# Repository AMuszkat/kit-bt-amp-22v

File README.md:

# kit_bt_amp_22v

A reference design demonstrating the **MA12070P amplifier** for portable applications, combining a **PSoC 6 MCU** with a **CYW-series Bluetooth module**.

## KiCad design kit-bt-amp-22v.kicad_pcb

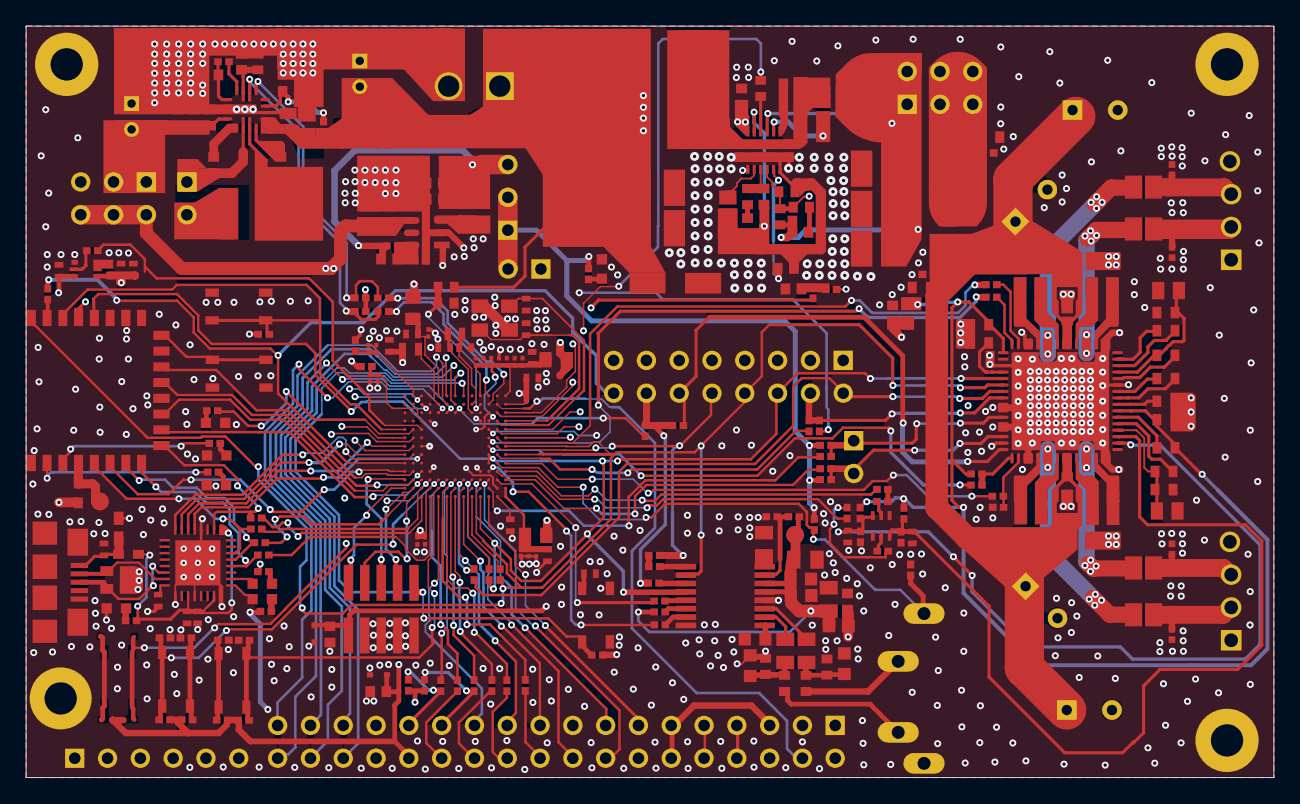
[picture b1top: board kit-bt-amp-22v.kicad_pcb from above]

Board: 4 copper layers, 96.6 x 58.2 mm, 274 parts (0 on the bottom side), 221 nets.

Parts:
C0A, C0B, C1A, C1B: C0402C471K5RAC; CAPC0402(1005)60_L
C1, C8, C19, C34, C80: CL10B104KB8NNNC; CAPC1608X90X30LL10T20
C2, C3, C4, C6, C7: GMK325BJ226MM-P; CAP1210_IPC_B
C5: EMZR350ARA470ME61G; PNSC-FT-V-53x53-2_V
C9, C11: CAPC1608X90X30LL10T20
C10: UMK212BB7225KG-T; CAPC2013X145X50LL20T25
C12: GRM1885C1H103JA01D; CAPC1608X90X30LL10T20
C13: GRM1885C1H682JA01D; CAPC1608X90X30LL10T20
C14, C16, C23, C26: CL05B104KA5NNNC; CAPC1608X90X30LL10T20
C15, C18: GRM21BR61E226ME44L; CAP0805_IPC_B
C17, C25: EST476M025AC3AA; FP-UPW1E220MDD-MFG
C20, C21, C27, C28: GRM188R61E106KA73J; CAP0603_IPC_C
C22: UMK105CG220JV-F; CAPC1608X90X30LL10T20
C24, C30: CL05B223KA5NNNC; CAPC1608X90X30LL10T20
C29: CL10B105KA8NFNC; CAPC1608X90X30LL10T20
C31, C32: C0402C102K5RACTU; FP-CL05A106MP5NUNC-MFG
C33, C75, C77: CL10B474KA8NFNC; CAPC1608X90N
C35, C40: CL05B104KA5NNNC; FP-CL05A106MP5NUNC-MFG
C36: CL05B103KO5NNNC; FP-CL05A106MP5NUNC-MFG
C37, C38, C41: CL05A105MO5NNNC; FP-CL05A106MP5NUNC-MFG
C39, C42: CL05A475MO5NUNC; FP-CL05A106MP5NUNC-MFG
C43, C46, C48: CL05A106MP5NUNC; FP-CL05A106MP5NUNC-MFG
C44, C49, C51, C53, C54, C56, C58, C59, C60, C62: GRM033R61A104ME15D; CAPC0603X33X15LL03T05
C45, C47: CL05A105KQ5NNNC; FP-CL05A106MP5NUNC-MFG
C50, C52, C55, C57, C61, C63, C81: CC0201KRX5R5BB105; CAPC0603X33X15LL03T05
C64, C65: UMK105CG220JV-F; FP-CL05A106MP5NUNC-MFG
C66: FP-CL05A106MP5NUNC-MFG
C67, C68: CC0402JRNPO9BN120; FP-CL05A106MP5NUNC-MFG
C69, C70: CL05A105MO5NNNC; CAPC1608X90X30LL10T20
C71, C72, C76, C78: TMK212BBJ106MG-T; CAPC2013X135N
C73, C74: CAPC1608X90N
C79: 10uF; CAPC2013X135N
C82: UMK105B7152KV-F; CAP0402_IPC_B
CAVDD0: CL10B105KA8NFNC; CAPC0603(1608)100_L
CCDC: CL10B105KA8NFNC; CAPC0603(1608)100_L
CCREF: CL10B105KA8NFNC; CAPC0603(1608)100_L
CF0A0, CF0A1, CF0B0, CF0B1, CF1A0, CF1A1, CF1B0, CF1B1: TMK212BBJ106MG-T; CAPC0805(2012)145_L
CFDC: CL10B105KA8NFNC; CAPC0603(1608)100_L
CFGD: CL10B104KB8NNNC; CAPC0603(1608)100_L
CGD0, CGD1: CL10B105KA8NFNC; CAPC0603(1608)100_L
CGD0N0, CGD1N0: CL10B104KB8NNNC; CAPC0603(1608)100_L
CGD0N1, CGD1N1: CL21B105KBFNNNG; CAPC0805(2012)145_L
CIN1, CIN4: UMK107BBJ225KA-T; CAPC0603(1608)100_L
CIN2, CIN3: GRM155R71H223KA12D; CAP0402_IPC_B
CPVDD0A, CPVDD1A: CL10B104KB8NNNC; CAPC0603(1608)100_L
CPVDD0B, CPVDD1B: CL21B105KBFNNNG; CAPC0805(2012)145_L
CSUP1, CSUP2, CSUP3, CSUP4: EEU-FS1V331LB; FP-EEU-FC1V221L-MFG
CT8: CL05B104KA5NNNC; CAPC1608X90X30LL10T20
CVGDC: CL10B105KA8NFNC; CAPC0603(1608)100_L
D1, D4: LTST-C191KSKT; LTST-C190TBKT-2_V
D2, D3: ESD5Z3.3T1G; ONSC-SOD-523-2-502-01_V
DS1, DS3: LTST-C191KSKT; LTST-C190TBKT-2_V
DS2: LTST-C191TBKT; LTST-C190TBKT-2_V
DS4: LTST-C190KGKT; LTST-C190TBKT-2_V
DS5: LTST-C190KRKT; LTST-C190TBKT-2_V
DVDD0: CL10B105KA8NFNC; CAPC0603(1608)100_L
J1, J2: 282834-4; HDRV4W85P254_4X1_1062X650X1000
J4: SJ1-3534NG; CUI_SJ1-3534NG
J_BCK_3V3: 826926-3; HDR1X3
J_BCK_5V: Header 3X2; HDR2X3
J_PVDD: Header 3X2; HDR2X3
J_USB1: 10118192-0001LF; FCI-10118192-0001LF-5_V
J_VCC_PSOC: 826936-2; HDR1X2
L0A, L0B, L1A, L1B: NFZ2MSD101SZ10L; FP-NFZ2MSD-IPC_B
L1: 7443330220; WE-HCC-1090
L2: NRS5030T4R7MMGJ
L3: LQM2MPN2R2MG0L; 6-0805_M
L4, L6: MPZ1608S331ATA00; SMD-0603
L5, L11: BLM18KG221SN1D; INDC1608X95N-2
L7: GLFR1608T2R2M-LR; SMD 0603-Low Profile
L8, L9, L10: BLM18KG102SN1D; MURA-BLM18PG_KG-B25-CHIP-2_V1
LSUP: 2743019447; WE-PBF, 7427930
MD1: CYBT-343026-01; FP-CYBT-343026-01-MFG
P1: Header 6; HDR1X6
P2: B2P-VH(LF)(SN); JST-B2P-VH(LF)(SN)_V
P4: Header 18X2; HDR2X18
P5: Header 2; HDR1X2
P6: MHDR2X5; FP-FTSH-105-01-F-DV-K-TR-MFG
P7: Header 8X2; HDR2X8
P_L2: 826936-2; HDR1X2
Q1: IRFHM830TRPbF; INF-PG-TSDSON-8-FL
Q2: BC846S; INF-SOT363_V
Q3: PMBT3946VPN,115; FP-SOT666-MFG
R1, R29, R46, R47, R52, R58, R76, R81, R82, R131, R132: ERJ-2GE0R00X; RESC1005X40X25NL05T10
R2: CRCW0603300KFKEA; RESC1608X55X30LL15T15
R3, R31, R32: RESC1608X55X30LL15T15
R4, R116, R117, R134: AC0402FR-074K75L; RESC1005X40X25NL05T10
R5: MCT06030Z0000ZP500; RESC1608X55X30LL15T15
R6: MCT06030C1782FP500; RESC1608X55X30LL15T15
R7: RT0603FRE0727KL; RESC1608X55X30LL15T15
R9: CRCW0402332KFKED; RESC1005X40X25NL05T10
R11: RC0402FR-07499KL; RESC1005X40X25NL05T10
R12: 541-73.2KLTR-ND; RESC1005X40X25NL05T10
R14, R34: CR0402-FX-1003GLF; RESC1005X40X25NL05T10
R16: CR0603-FX-2152ELF; RESC1608X55X30LL15T15
R17, R18: RC0402FR-0759KL; RESC1005X40X25NL05T10
R19, R20: RC0402FR-076K8L; RESC1005X40X25NL05T10
R21, R24: RC0402FR-07150KL; RESC1005X40X25NL05T10
R22, R23, R35, R42, R43, R49, R70: MCS0402MC1002FE000; RESC1005X40X25NL05T10
R25, R36, R37, R38, R112: RC0402FR-071K3L; RESC1005X40X25NL05T10
R26, R27: RC0603JR-070RL; RESC1608X55X30LL15T15
R28, R30, R33, R53, R55, R56, R59, R60, R61, R62, R63, R64, R65, R67, R79, R80, R83, R85, R86, R89, R90, R93, R94, R96: CRCW040249R9FKEDC; RESC1005X40X25NL05T10
R39, R40, R41: CG0603MLC-05LE; FP-CG0603-MFG
R44: CRCW0402200RFKEDC; RESC1005X40X25NL05T10
R45: CRCW04021K00FKEDC; RESC1005X40X25NL05T10
R48: ERA-3AEB124V; RESC1608X55X30LL15T15
R50, R51, R54, R57, R66, R68, R69, R71, R74, R75: RESC1005X40X25NL05T10
R114, R115: ERJ-2RKF5761X; RESC1005X40X25NL05T10
R133: ERA-3AEB1073V; RESC1608X55X30LL15T15
RT1: CRCW040245K3FKEDC; RESC1005X40X25NL05T10
RT8: MCS0402MC1002FE000; RESC1005X40X25NL05T10
SW1, SW3: SKRPABE010; SKRPACE011
SW_BT_RES: SKRPABE010; SKRPACE011
SW_RECOVER: SKRPABE010; SKRPACE011
SW_RES: SKRPABE010; SKRPACE011
TP_AKVDD: TP
TP_BTVDDIN: TP
TP_VCC_PSOC: TP; TP-06mm
U1: MA12070P1; QFN50P900X900X100_HS-65N
U2: AK5720VT; TSSOP16
U3: MP3428AGL
U4: MP8860GQ-0000; MP8860
U5: AP3419KTTR-G1; FP-TSOT26-IPC_B
U7: CY7C65215-32LTXI; CYP-LTX32_M
U8: CY8C624ABZI-S2D44; BGA124C65P13X13_900X900X100
Y1: ABS05-32.768KHZ-9-T; FP-ABS05-MFG
Y2: ABM8-18.432MHZ-D1X-T; FP-ABM8-MFG

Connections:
5V_VBUS: C39.1, C40.1, L4.2, R36.2, U7.1, U7.19, U7.23
AK_FSEL: R28.2, U8.C10
AK_GSEL: R51.1, R52.1, U2.7
AK_I2S_BCLK: MD1.5, P7.6, R86.2, U1.21, U2.12, U8.C8, U8.C9, U8.D13
AK_I2S_MCLK: R132.2, U2.11
AK_I2S_SDO: R33.2, R82.1
AK_I2S_WS: MD1.1, P7.8, R90.2, U1.22, U2.10, U8.A7, U8.A8, U8.D12
AK_PDN: R30.2, U8.B11
AK_PLUG_DTC: C82.1, J4.4, R34.1, U8.B9
AK_VDD: C75.2, C76.2, C77.2, C78.2, L11.2, R29.2, R51.2, TP_AKVDD.1, U2.5, U2.6
BATT_LEV: R48.1, R133.2, U8.D2
BST_EN: R5.2, U8.A3
BT_CTS: MD1.17, R69.2, U7.28
BT_GPIO3: MD1.22, R38.2
BT_GPIO6: MD1.23, R37.2
BT_GPIO7: MD1.19, U8.N10
BT_I2S_SDI: MD1.4, R1.2
BT_I2S_SDO: MD1.2, R81.1
BT_PWR: R42.2, U8.L5
BT_RES: MD1.3, R43.2, SW_BT_RES.1, SW_BT_RES.2, U8.N5
BT_RTS: MD1.18, R74.2, U7.29
BT_RX: MD1.20, R68.2, U7.30
BT_TX: MD1.16, R66.2, U7.2
BT_VDD: C38.1, L6.1, Q3.3
BT_VDDIN: L6.2, MD1.21, TP_BTVDDIN.1
CLK_HF5: P7.14, R56.2, R131.1, R132.1
CTS1: U7.7, U8.N8
ECO_P12_6: C67.2, U8.A4, Y2.3
ECO_P12_7: C68.1, U8.B4, Y2.1
GND: C0A.1, C0B.2, C1A.1, C1B.2, C2.2, C3.2, C4.2, C5.2, C6.2, C7.2, C8.1, C15.2, C16.2, C17.1, C18.2, C19.1, C20.2, C21.2, C24.2, C25.1, C26.2, C27.2, C28.2, C29.1, C30.2, C31.1, C32.1, C33.2, C34.1, C35.2, C36.2, C37.2, C38.2, C39.2, C40.2, C41.2, C42.2, C43.2, C44.1, C45.2, C46.2, C47.2, C48.2, C49.1, C50.1, C51.1, C52.1, C53.1, C54.1, C55.1, C56.1, C57.1, C58.1, C59.1, C60.1, C61.1, C62.1, C63.1, C64.1, C65.1, C66.1, C67.1, C68.2, C69.1, C70.1, C73.1, C74.1, C75.1, C76.1, C77.1, C78.1, C79.1, C80.1, C81.1, C82.2, CAVDD0.1, CCDC.2, CCREF.1, CGD0N0.2, CGD0N1.1, CGD1N0.2, CGD1N1.1, CIN1.1, CIN2.2, CIN3.2, CIN4.1, CPVDD0A.1, CPVDD0B.1, CPVDD1A.1, CPVDD1B.1, CSUP1.2, CSUP2.2, CSUP3.2, CSUP4.2, CT8.2, D1.2, D2.2, D3.2, D4.2, DS1.2, DS2.2, DS3.2, DVDD0.1, J1.1, J1.4, J2.1, J2.4, J4.1, J_BCK_5V.5, J_USB1.5, J_USB1.6, J_USB1.7, J_USB1.8, J_USB1.9, J_USB1.10, J_USB1.11, MD1.7, MD1.13, MD1.24, P2.2, P4.1, P4.6, P4.14, P4.17, P4.29, P4.30, P6.3, P6.5, P6.7, P6.9, P7.1, P7.3, P7.5, P7.7, P7.9, P7.11, P7.13, P7.15, Q2.1, Q2.4, Q3.1, R12.2, R16.1, R17.2, R21.1, R24.1, R31.2, R32.2, R39.2, R40.2, R41.2, R52.2, R57.1, R58.1, R75.1, R76.1, R133.1, SW_BT_RES.3, SW_BT_RES.4, SW_RECOVER.3, SW_RECOVER.4, SW_RES.3, SW_RES.4, U1.1, U1.2, U1.13, U1.14, U1.19, U1.25, U1.26, U1.28, U1.29, U1.31, U1.35, U1.36, U1.47, U1.48, U1.59, U1.65, U2.4, U2.16, U3.9, U3.10, U3.17, U3.18, U3.22, U4.2, U4.10, U4.11, U5.2, U7.4, U7.17, U7.20, U7.24, U7.33, U8.B12, U8.C3, U8.D4, U8.D10, U8.K4, U8.K10, Y2.2, Y2.4
I2S0_RX_SD: P7.16, R81.2, U8.N9
I2S0_TX_SD: P7.2, R94.2, U1.23
I2S1_RX_SD: P7.10, R82.2, U8.B7
I2S1_TX_SD: P7.4, R1.1, R83.2, U1.24
MA_CLIP: R67.2, U1.15
MA_ENABLE: R18.1, R61.2, U1.33
MA_ERROR: R65.2, U1.16
MA_I2S_MCLK: P7.12, R131.2, U1.32
MA_MSEL0: C31.2, Q2.3, R19.1, R21.2, U1.51
MA_MSEL1: C32.2, Q2.6, R20.1, R24.2, U1.50
MA_MUTE: R17.1, R62.2, U1.34
MA_PVDD: CIN3.1, CIN4.2, CPVDD0A.2, CPVDD0B.2, CPVDD1A.2, CPVDD1B.2, CSUP1.1, CSUP2.1, CSUP3.1, CSUP4.1, LSUP.2, U1.7, U1.8, U1.41, U1.42
MA_SCL: P5.1, R53.2, R114.1, U1.27
MA_SDA: P5.2, R55.2, R115.1, U1.30
MA_VDD: CAVDD0.2, CVGDC.2, DVDD0.2, L5.2, R18.2, R19.2, R20.2, U1.17, U1.55
MISO1: MD1.12, U8.L10
MISO2: P4.20, R89.1
MOSI1: MD1.11, U8.M10
MOSI2: P4.22, R85.1
MP_AGND: C10.1, C11.1, C12.1, C13.1, R6.1, U3.5, U3.16
MP_SCL: R4.1, R59.2, U4.5
MP_SDA: R60.2, R134.1, U4.6
MP_VCC: C29.2, R14.1, U4.9
MSEL0: R22.2, R63.2
MSEL1: R23.2, R64.2
NetC1_1: C1.1, L1.2, Q1.1, Q1.2, Q1.3, U3.7, U3.8, U3.19, U3.20, U3.21
NetC1_2: C1.2, U3.1
NetC2_1: C2.1, C3.1, C4.1, C9.2, J_PVDD.1, J_PVDD.2, Q1.5, Q1.6, Q1.7, Q1.8, R2.2, U3.3
NetC9_1: C9.1, R3.2
NetC10_2: C10.2, U3.12
NetC11_2: C11.2, R7.2, U3.13
NetC12_2: C12.2, U3.15
NetC13_2: C13.2, R7.1
NetC14_1: C14.1, L2.1, U4.15
NetC14_2: C14.2, U4.16
NetC20_1: C20.1, C21.1, C22.2, J_BCK_3V3.3, L3.2, R9.1
NetC22_1: C22.1, R9.2, R12.1, U5.6
NetC23_1: C23.1, P_L2.1, U4.14
NetC23_2: C23.2, U4.13
NetC24_1: C24.1, R11.2, U4.3
NetC25_2: C25.2, C26.1, C27.1, C28.1, J_BCK_5V.1, J_BCK_5V.3, U4.12
NetC30_1: C30.1, R16.2, U4.7
NetC33_1: C33.1, U2.1
NetC36_1: C36.1, J_USB1.1, L4.1, R41.1
NetC41_1: C41.1, U7.16
NetC66_2: C66.2, SW_RES.2
NetC71_1: C71.1, U2.2
NetC71_2: C71.2, C73.2, R26.2, R31.1
NetC72_1: C72.1, U2.3
NetC72_2: C72.2, C74.2, R27.2, R32.1
NetC79_2: C79.2, U2.8
NetCCDC_1: CCDC.1, U1.56
NetCCREF_2: CCREF.2, U1.20
NetCF0A0_1: CF0A0.1, CF0A1.1, U1.3
NetCF0A0_2: CF0A0.2, CF0A1.2, U1.6
NetCF0B0_1: CF0B0.1, CF0B1.1, U1.9
NetCF0B0_2: CF0B0.2, CF0B1.2, U1.12
NetCF1A0_1: CF1A0.1, CF1A1.1, U1.46
NetCF1A0_2: CF1A0.2, CF1A1.2, U1.43
NetCF1B0_1: CF1B0.1, CF1B1.1, U1.40
NetCF1B0_2: CF1B0.2, CF1B1.2, U1.37
NetCFDC_1: CFDC.1, U1.58
NetCFDC_2: CFDC.2, U1.57
NetCFGD_1: CFGD.1, U1.63
NetCFGD_2: CFGD.2, U1.62
NetCGD0_1: CGD0.1, CGD0N0.1, CGD0N1.2, U1.61
NetCGD0_2: CGD0.2, U1.60
NetCGD1_1: CGD1.1, U1.53
NetCGD1_2: CGD1.2, CGD1N0.1, CGD1N1.2, U1.52
NetCT8_1: CT8.1, RT1.2, RT8.2
NetCVGDC_1: CVGDC.1, U1.54
NetD1_1: D1.1, R25.1
NetD4_1: D4.1, R112.1
NetDS1_1: DS1.1, R37.1
NetDS2_1: DS2.1, R38.1
NetDS3_1: DS3.1, R36.1
NetDS4_1: DS4.1, R44.1
NetDS4_2: DS4.2, U7.26
NetDS5_1: DS5.1, R45.1
NetDS5_2: DS5.2, U7.25
NetL2_2: L2.2, P_L2.2
NetL3_1: L3.1, U5.3
NetL7_1: L7.1, U8.J2
NetQ1_4: Q1.4, U3.2
NetQ2_2: Q2.2, R23.1
NetQ2_5: Q2.5, R22.1
NetQ3_2: Q3.2, R42.1
NetQ3_5: Q3.5, Q3.6, R35.2
NetR2_1: R2.1, R3.1, R6.2, RT1.1, U3.14
NetR5_1: R5.1, U3.4
NetR14_2: R14.2, U4.8
NetR28_1: R28.1, U2.15
NetR29_1: R29.1, U2.14
NetR30_1: R30.1, U2.13
NetR33_1: R33.1, U2.9
NetR50_1: R50.1, R58.2, SW1.3, SW1.4
NetR53_1: R53.1, U8.C12
NetR55_1: R55.1, U8.A11
NetR56_1: R56.1, U8.G3
NetR59_1: R59.1, U8.C2
NetR60_1: R60.1, U8.C1
NetR61_1: R61.1, U8.C7
NetR62_1: R62.1, U8.A9
NetR63_1: R63.1, U8.A10
NetR64_1: R64.1, U8.B10
NetR65_1: R65.1, U8.C6
NetR66_1: R66.1, U8.L13
NetR67_1: R67.1, U8.B6
NetR68_1: R68.1, U8.L12
NetR69_1: R69.1, U8.K13
NetR71_1: R71.1, R76.2, SW3.3, SW3.4
NetR74_1: R74.1, U8.N13
NetR79_1: R79.1, U8.G11
NetR80_1: R80.1, U8.G12
NetR83_1: R83.1, U8.B8
NetR85_2: R85.2, U8.H13
NetR86_1: R86.1, U8.E12
NetR89_2: R89.2, U8.H12
NetR90_1: R90.1, U8.E13
NetR93_2: R93.2, U8.H11
NetR94_1: R94.1, U8.F11
NetR96_2: R96.2, U8.G13
OUT0A: L0A.1, U1.4, U1.5
OUT0B: L0B.1, U1.10, U1.11
OUT1A: L1B.1, U1.44, U1.45
OUT1B: L1A.1, U1.38, U1.39
P1_0: P4.31, U8.G2
P1_1: P4.32, U8.G1
P1_2: P4.34, U8.H3
P1_3: P4.36, U8.H2
P1_4: P4.33, U8.H1
P1_5: P4.35, U8.J3
P3_4: P1.4, U8.M6
P3_5: P1.3, U8.N6
P4_0: P1.6, U8.L7
P4_1: P1.5, U8.M7
P7_5: P4.23, U8.J13
P8_6: P4.19, U8.F13
P8_7: P4.21, U8.F12
P9_0: P4.18, U8.E11
P9_6: P4.15, U8.D11
P9_7: P4.13, U8.C13
P10_3: P4.16, U8.C11
P12_0: P4.3, U8.A6
P12_3: P4.2, U8.A5
P12_4: P4.7, P4.8, U8.B5
P12_5: P4.9, P4.10, U8.C5
P13_3: P4.4, U8.B2
PSOC_LED1: R112.2, U8.M5
PSOC_USBDM: P1.1, U8.L1
PSOC_USBDP: P1.2, U8.L2
PVDD: CIN1.2, CIN2.1, J_PVDD.3, J_PVDD.4, J_PVDD.5, J_PVDD.6, LSUP.1
PWM_1: RT8.1, U8.B3
RECOVER: MD1.9, SW_RECOVER.1, SW_RECOVER.2
RTS1: U7.8, U8.M8
RX1: U7.6, U8.N7
SCL1: P4.25, R80.2, R116.1
SCLK1: MD1.15, U8.L11
SCLK2: P4.26, R93.1
SDA1: P4.27, R79.2, R117.1
SPEAK0A: C0A.2, J1.2, L0A.2
SPEAK0B: C0B.1, J1.3, L0B.2
SPEAK1A: C1A.2, J2.3, L1B.2
SPEAK1B: C1B.1, J2.2, L1A.2
SS0_1: MD1.14, U8.M11
SS0_2: P4.24, R96.1
SW2: R49.1, R57.2, SW1.1, SW1.2, U8.J12
SW4: R70.1, R75.2, SW3.1, SW3.2, U8.J11
SWDCLK: P6.4, U8.M13
SWDIO: P6.2, U8.N12
TDI: P6.8, U8.M12
TDO_SWO: P6.6, U8.N11
TX1: U7.5, U8.L8
USB_DM: J_USB1.2, R40.1, U7.15
USB_DP: J_USB1.3, R39.1, U7.14
VBAT: C5.1, C6.1, C7.1, C8.2, C15.1, C16.1, C17.2, L1.1, P2.1, R11.1, R48.2, U3.6, U3.11, U4.1
VBUCK: C42.1, C47.1, L7.2, U8.A2
VCC_3V3: C35.1, C37.1, J_BCK_3V3.1, J_BCK_3V3.2, J_VCC_PSOC.2, Q3.4, R4.2, R25.2, R34.2, R35.1, R43.1, R44.2, R45.2, R114.2, R115.2, R116.2, R117.2, R134.2
VCC_5V: C18.1, C19.2, C34.2, C80.2, J_BCK_5V.2, J_BCK_5V.4, J_BCK_5V.6, L5.1, L11.1, U5.1, U5.4
VCC_PSOC: C69.2, C70.2, D2.1, D3.1, J_VCC_PSOC.1, L8.1, L9.1, L10.1, P4.5, P4.11, P4.12, P4.28, P6.1, R49.2, R50.2, R54.1, R70.2, R71.2, TP_VCC_PSOC.1
VDDA: C48.1, C53.2, C54.2, C55.2, L10.2, U8.A12, U8.A13
VDDD: C44.2, C46.1, C49.2, C50.2, C59.2, C60.2, C61.2, C62.2, C63.2, C81.2, L9.2, R46.2, R47.2, U8.A1, U8.C4, U8.D1, U8.K12
VDDIO2: C51.2, C52.2, R46.1, U8.L4
VDDUSB: C56.2, C57.2, R47.1, U8.M1
VDD_NS: C43.1, C58.2, L8.2, U8.J1
VREF: C45.1, U8.B13
Vin_L: J4.2, R26.1
Vin_R: J4.3, R27.1
WCO_P0_0: C65.2, U8.E2, Y1.1
WCO_P0_1: C64.2, U8.E3, Y1.2
XRES: P6.10, R54.2, SW_RES.1, U8.F1
